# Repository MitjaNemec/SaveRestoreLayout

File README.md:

# KiCad Save Restore Layout plugin

> [!NOTE]
> The functionality of this plugin is now available in KiCad natively! As such, this plugin is no longer updated. For details on KiCad's multichannel implementation, see [official KiCad documentation](https://docs.kicad.org/10.0/en/pcbnew/pcbnew.html#pcb-design-blocks).

This plugin implements footprint modules or snippets feature. The plugin saves partial layout corresponding to footprints from one hierarchical sheet so that it can be restored in other projects. All projects have to use the same hierarchical sheet schematics. If the schematics has been edited, the plugin will refuse to restore the layout. So in projects where you need to change the schematics slightly, first restore the layout and then change the schematics.

## Installation

The preferred way to install the plugin is via KiCad's PCM (Plugin and Content Manager). Installation on non-networked
can be done by downloading the latest [release](https://github.com/MitjaNemec/SaveRestoreLayout/releases) and installing
in with PCM with `Install from file` option 

## Warning

There is a [bug](https://gitlab.com/kicad/code/kicad/-/issues/11076) in KiCad when reusing hierarchical sheets which contain multiple instances of same nested sheet. the bug causes unintended changes in schematics files, which will cause the plugin to fail. Please read the bug description which also contains a workaround for such cases.

**Author :** doc.dr. Mitja Nemec

**Date :** 2025

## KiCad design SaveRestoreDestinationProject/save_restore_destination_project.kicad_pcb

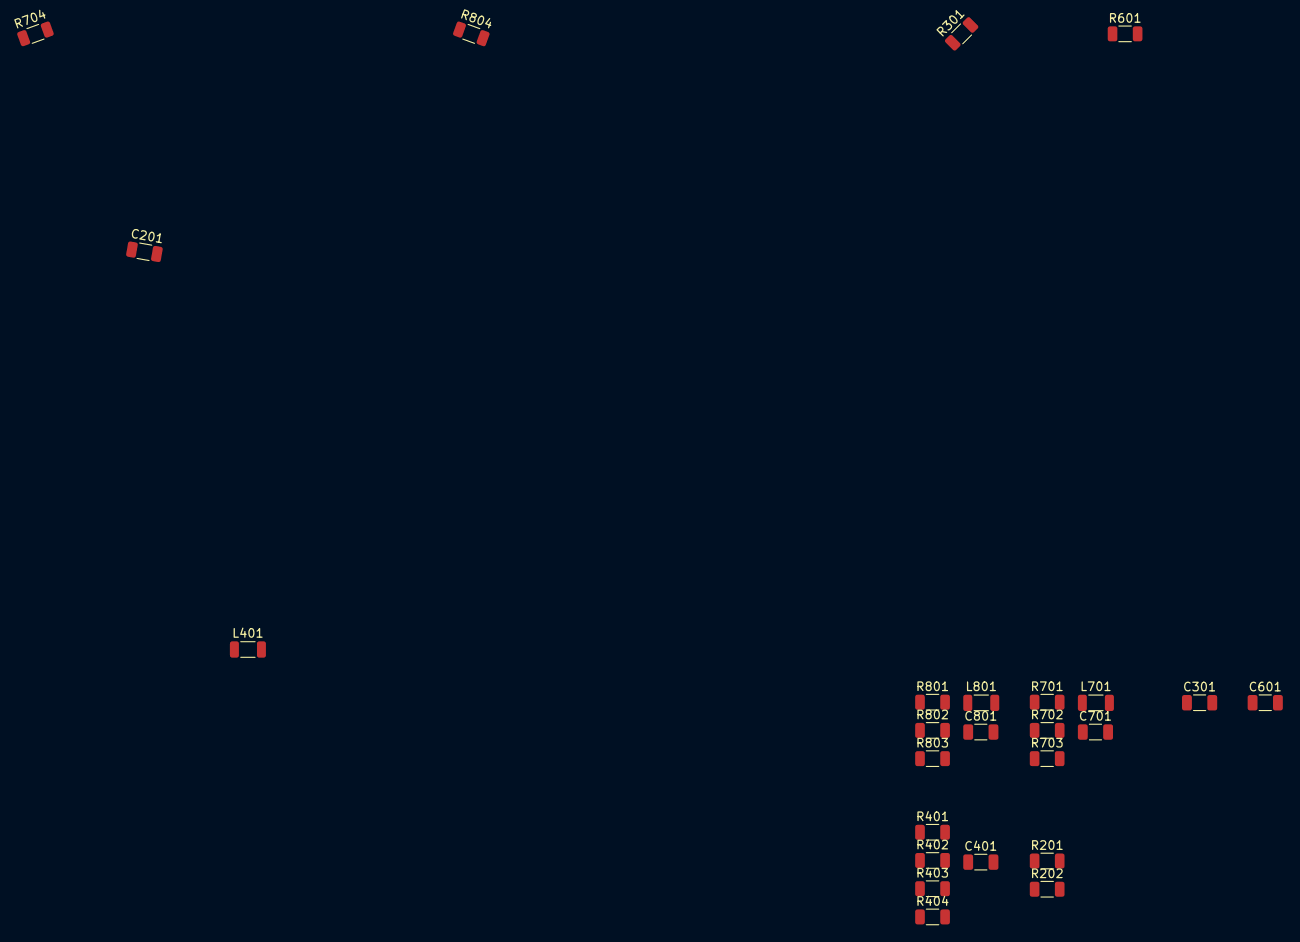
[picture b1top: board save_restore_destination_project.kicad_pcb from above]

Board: 2 copper layers, 25 parts (0 on the bottom side), 15 nets, no tracks yet.

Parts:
C201, C301, C401, C601, C701, C801: C; C_1206_3216Metric
L401, L701, L801: L; L_1206_3216Metric
R201, R202, R301, R401, R402, R403, R404, R601, R701, R702, R703, R704, R801, R802, R803, R804: R; R_1206_3216Metric

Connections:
+5V: R402.2, R702.2, R802.2
/local_1/local_2_a/in: R201.2, R701.1
/local_1/local_2_a/mid: L701.2, R703.2, R704.1
/local_1/local_2_a/out: C201.1, C701.1, R704.2
/local_1/local_2_b/in: C201.2, R801.1
/local_1/local_2_b/mid: L801.2, R803.2, R804.1
/local_1/local_2_b/out: C801.1, R202.1, R804.2
/local_2/mid: L401.2, R403.2, R404.1
/local_2/out: C401.1, R404.2
/relative_1/out: C301.1, R301.2
/relative_2/out: C601.1, R601.2
GND: C301.2, C401.2, C601.2, C701.2, C801.2, R403.1, R703.1, R803.1
unnamed: L401.1, R401.2, R402.1
unnamed: L701.1, R701.2, R702.1
unnamed: L801.1, R801.2, R802.1

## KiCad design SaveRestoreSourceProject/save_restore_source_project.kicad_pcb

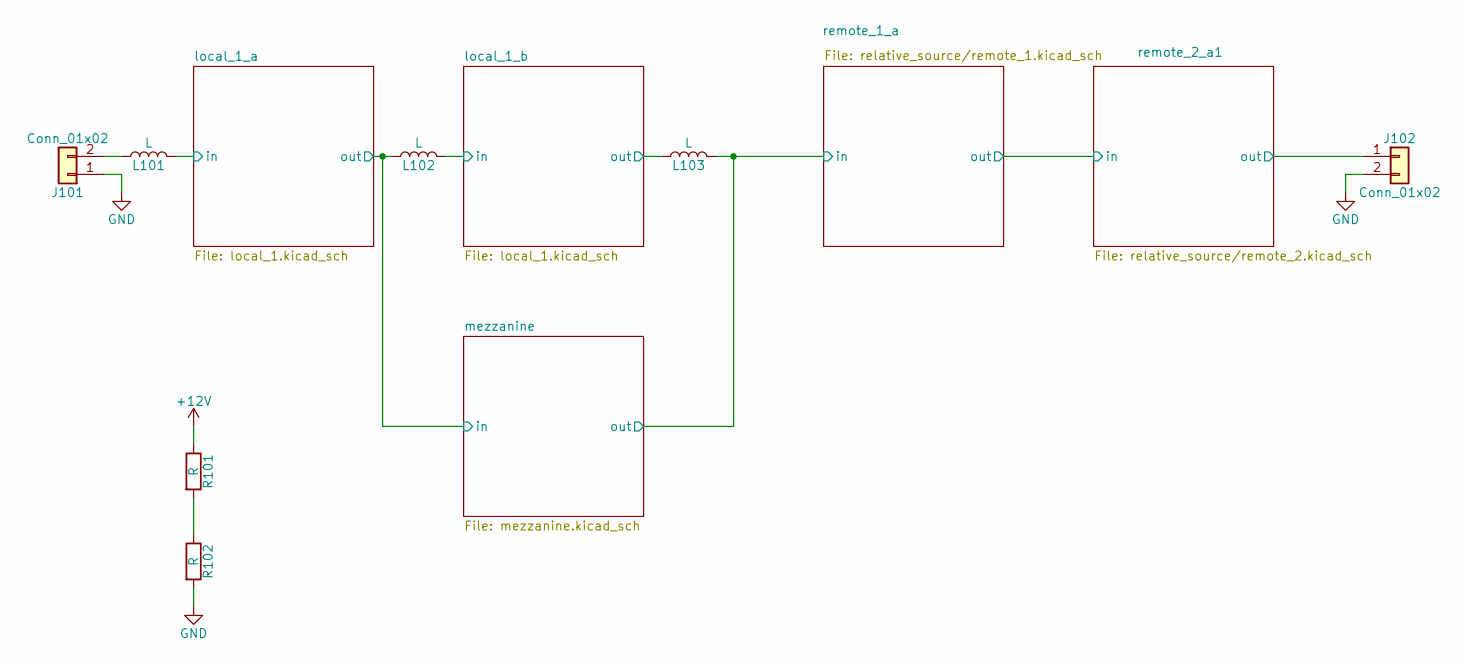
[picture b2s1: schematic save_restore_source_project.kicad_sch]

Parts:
J101, J102: Conn_01x02; PinHeader_1x02_P2.54mm_Vertical
L101, L102, L103: L; L_1206_3216Metric
R101, R102: R; R_1206_3216Metric

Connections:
+12V: R101.1
/local_1_a/in: L101.2; also elsewhere on the board
/local_1_a/out: L102.1; also elsewhere on the board
/local_1_b/in: L102.2; also elsewhere on the board
/local_1_b/out: L103.1; also elsewhere on the board
/mezzanine/out: L103.2; also elsewhere on the board
/remote_2_a1/out: J102.1; also elsewhere on the board
GND: J101.1, J102.2, R102.2; also elsewhere on the board
unnamed: J101.2, L101.1
unnamed: R101.2, R102.1

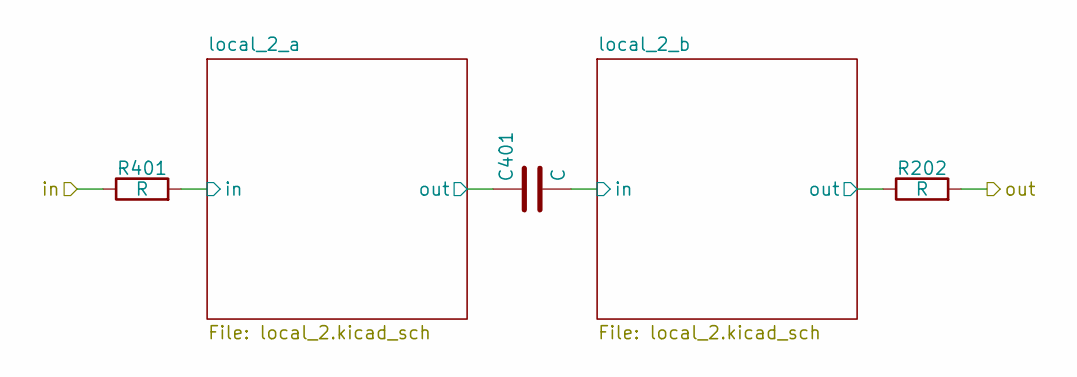
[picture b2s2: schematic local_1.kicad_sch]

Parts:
C401: C; C_1206_3216Metric
R202, R401: R; R_1206_3216Metric

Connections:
/local_1_a/local_2_b/out: R202.1; also elsewhere on the board
/local_1_a/out: R202.2; also elsewhere on the board
/local_1_b/in: R401.1; also elsewhere on the board
/local_1_b/local_2_a/in: R401.2; also elsewhere on the board
/local_1_b/local_2_a/out: C401.1; also elsewhere on the board
/local_1_b/local_2_b/in: C401.2; also elsewhere on the board

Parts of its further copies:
C201: C; C_1206_3216Metric
R201, R402: R; R_1206_3216Metric

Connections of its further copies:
/local_1_a/in: R201.1; also elsewhere on the board
/local_1_a/local_2_a/in: R201.2; also elsewhere on the board
/local_1_a/local_2_a/out: C201.1; also elsewhere on the board
/local_1_a/local_2_b/in: C201.2; also elsewhere on the board
/local_1_b/local_2_b/out: R402.1; also elsewhere on the board
/local_1_b/out: R402.2; also elsewhere on the board

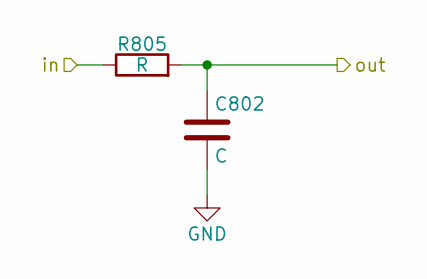
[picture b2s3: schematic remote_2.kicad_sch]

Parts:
C802: C; C_1206_3216Metric
R805: R; R_1206_3216Metric

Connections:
/mezzanine/out: R805.1; also elsewhere on the board
/remote_1_a/out: C802.1, R805.2; also elsewhere on the board
GND: C802.2; also elsewhere on the board

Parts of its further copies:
C1401: C; C_1206_3216Metric
R1401: R; R_1206_3216Metric

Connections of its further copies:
/remote_1_a/out: R1401.1; also elsewhere on the board
/remote_2_a1/out: C1401.1, R1401.2; also elsewhere on the board
GND: C1401.2; also elsewhere on the board

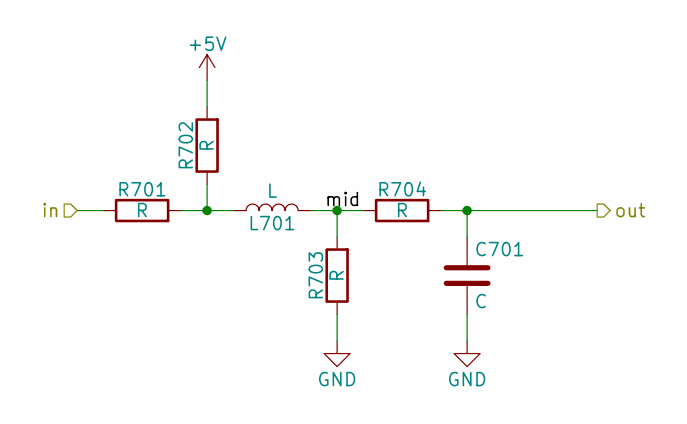
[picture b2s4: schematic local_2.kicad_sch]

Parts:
C701: C; C_1206_3216Metric
L701: L; L_1206_3216Metric
R701, R702, R703, R704: R; R_1206_3216Metric

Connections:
+5V: R702.2; also elsewhere on the board
/local_1_a/local_2_a/in: R701.1; also elsewhere on the board
/local_1_a/local_2_a/mid: L701.2, R703.2, R704.1
/local_1_a/local_2_a/out: C701.1, R704.2; also elsewhere on the board
GND: C701.2, R703.1; also elsewhere on the board
unnamed: L701.1, R701.2, R702.1

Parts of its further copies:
C301, C801, C901, C1001, C1101: C; C_1206_3216Metric
L301, L801, L901, L1001, L1101: L; L_1206_3216Metric
R301, R302, R303, R304, R801, R802, R803, R804, R901, R902, R903, R904, R1001, R1002, R1003, R1004, R1101, R1102, R1103, R1104: R; R_1206_3216Metric

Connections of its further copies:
+5V: R302.2, R802.2, R902.2, R1002.2, R1102.2; also elsewhere on the board
/local_1_a/local_2_b/in: R301.1; also elsewhere on the board
/local_1_a/local_2_b/mid: L301.2, R303.2, R304.1
/local_1_a/local_2_b/out: C301.1, R304.2; also elsewhere on the board
/local_1_b/local_2_a/in: R801.1; also elsewhere on the board
/local_1_b/local_2_a/mid: L801.2, R803.2, R804.1
/local_1_b/local_2_a/out: C801.1, R804.2; also elsewhere on the board
/local_1_b/local_2_b/in: R901.1; also elsewhere on the board
/local_1_b/local_2_b/mid: L901.2, R903.2, R904.1
/local_1_b/local_2_b/out: C901.1, R904.2; also elsewhere on the board
/mezzanine/local_mezzanine/local_2_a1/in: R1001.1; also elsewhere on the board
/mezzanine/local_mezzanine/local_2_a1/mid: L1001.2, R1003.2, R1004.1
/mezzanine/local_mezzanine/local_2_a1/out: C1001.1, R1004.2; also elsewhere on the board
/mezzanine/local_mezzanine/local_2_b1/in: R1101.1; also elsewhere on the board
/mezzanine/local_mezzanine/local_2_b1/mid: L1101.2, R1103.2, R1104.1
/mezzanine/local_mezzanine/local_2_b1/out: C1101.1, R1104.2; also elsewhere on the board
GND: C301.2, C801.2, C901.2, C1001.2, C1101.2, R303.1, R803.1, R903.1, R1003.1, R1103.1; also elsewhere on the board
unnamed: L301.1, R301.2, R302.1
unnamed: L801.1, R801.2, R802.1
unnamed: L901.1, R901.2, R902.1
unnamed: L1001.1, R1001.2, R1002.1
unnamed: L1101.1, R1101.2, R1102.1

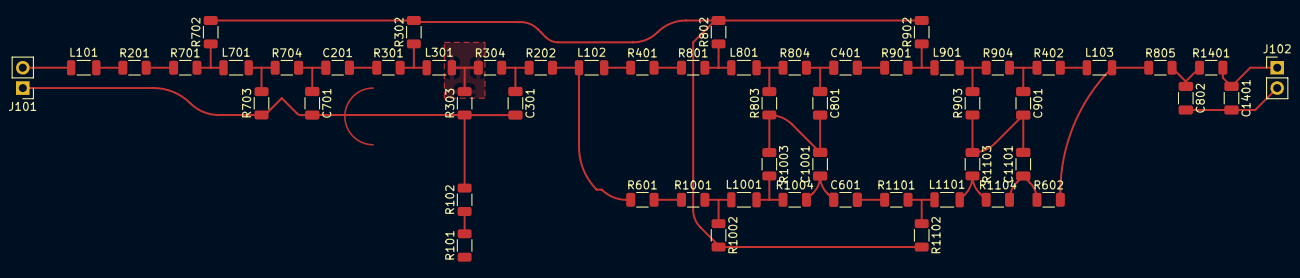
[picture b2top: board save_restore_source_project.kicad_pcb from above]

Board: 2 copper layers, 56 parts (0 on the bottom side), 35 nets.

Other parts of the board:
C601: C; C_1206_3216Metric
R601, R602: R; R_1206_3216Metric

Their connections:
/local_1_a/out: R601.1; also elsewhere on the board
/mezzanine/local_mezzanine/local_2_a1/in: R601.2; also elsewhere on the board
/mezzanine/local_mezzanine/local_2_a1/out: C601.1; also elsewhere on the board
/mezzanine/local_mezzanine/local_2_b1/in: C601.2; also elsewhere on the board
/mezzanine/local_mezzanine/local_2_b1/out: R602.1; also elsewhere on the board
/mezzanine/out: R602.2; also elsewhere on the board

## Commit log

2022-03-29 Initial commit. backend save and restore functionality works
2022-04-09 Resolved SaveBoard/LoadBoard issues. Still needs further testing
2022-04-09 Removed unused code for saving/loading boardfiles
2022-04-09 Add option to select what is saved and how much is saved
2022-04-09 update packaging code
2022-04-10 Fix the item selection logic whan saving layout
2022-04-11 Add check for copper layer count, and saved layout version number
2022-04-12 Bugfix to enable saving of drawings and text items when they are intersectiong the bounding box
2022-04-12 Bump version
2022-04-13 Add README.md
2022-05-04 Fix GUI issues on Windows
2022-10-10 Fix problem with footprints missing the sheetfile and sheetname properties
    This problem is currently caused by e.g. the KiBuzzard plugin that creates
    footprints that have neither the sheetfile nor sheetname properties set.
2022-10-16 test for existense of Sheetfile and Sheetname properties in footprints.
    Fixes: #4
2022-10-16 List only one (latest) version in metadata
2022-10-24 Wrap running of save layout in try/except to catch any exception an produce user friendly error message
2022-10-24 Add custom dialog with URL to the plugin repository
2022-10-30 fixed typo in README.md
2022-11-04 update build script
2022-11-04 Change the default filename suggestion when saving layout
2022-11-04 Commented out .png file regeneration on each release. There is something funny going on with teh specific .svg file that results in blurry png files for this plugin only
2022-11-30 Add schematic parsing (conditional)
2023-01-10 Version that runs on V7
2023-01-10 update KiCad version
2023-01-11 Added a grouping function, so all items of a restored layout are grouped and can be handled like a single block
2023-01-15 add a GUI to set optiona group name when restoring
2023-01-15 add a GUI to set optional group name when restoring
2023-01-16 fix typo in metadata.json
2023-01-20 remove wxhyperlinkctrl
2023-01-23 Revert removal of wxhyperlinkctrl
2023-02-25 Fix schematics parsing
2023-04-03 Better schematics filename handling
2023-05-17 Fixt the KiCad's python API changes in 7.0.2
2023-10-11 Updated the test projects
2023-10-11 Properly handle hierarchical sheets without footprints, change hash calculation (reject all instances)
2023-10-11 update test_project_files
2023-10-11 save and restore works as expected with new hash
2023-10-12 added some logging
2024-01-13 V7.99 compatibility fixes: - schematic parsing code updated - FP_TEXT -> PCB_TEXT - fp sheetname/sheetfile properties foundations for change to json format save instead of pickle
2024-01-24 Add support for connected drawings, update test template
2024-01-25 Change sorting and and find anchor fp with robust search
2024-01-25 refactor footprint matching
2025-04-02 KiCad V9 compatible release
2025-04-02 V9 compatibility change
2026-04-08 Dodal avtorstvo
    Added author and date information to README.
2026-04-08 Fix formatting in author and date sections
2026-04-08 Rename plugin to KiCad Save Restore Layout
2026-04-08 Update date in README to 2025
